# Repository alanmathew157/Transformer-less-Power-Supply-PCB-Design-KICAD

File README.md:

# TRANSFORMER LESS POWER SUPPLY PCB Design using KICAD -ALTIMUM
## PCB TOP VIEW

## PCB BOTTOM VIEW

## Project Overview
This project is a transformerless power supply designed in KiCad as part of my PCB design learning journey. Instead of using a bulky step-down transformer, the circuit employs a capacitive dropper (C4) to limit the AC current from the mains supply. The series resistor helps limit inrush current and improve safety. The reduced AC signal is then rectified using a full-wave bridge rectifier composed of four 1N4007 diodes, converting it into pulsating DC. Filter capacitors (C1, C2, and C3) smooth the rectified voltage by reducing ripple. Zener diodes provide voltage clamping and protection against overvoltage conditions. Finally, an LM7805 linear voltage regulator produces a stable 5V DC output suitable for low-power electronic applications. An LED indicator with a current-limiting resistor confirms the presence of output voltage.

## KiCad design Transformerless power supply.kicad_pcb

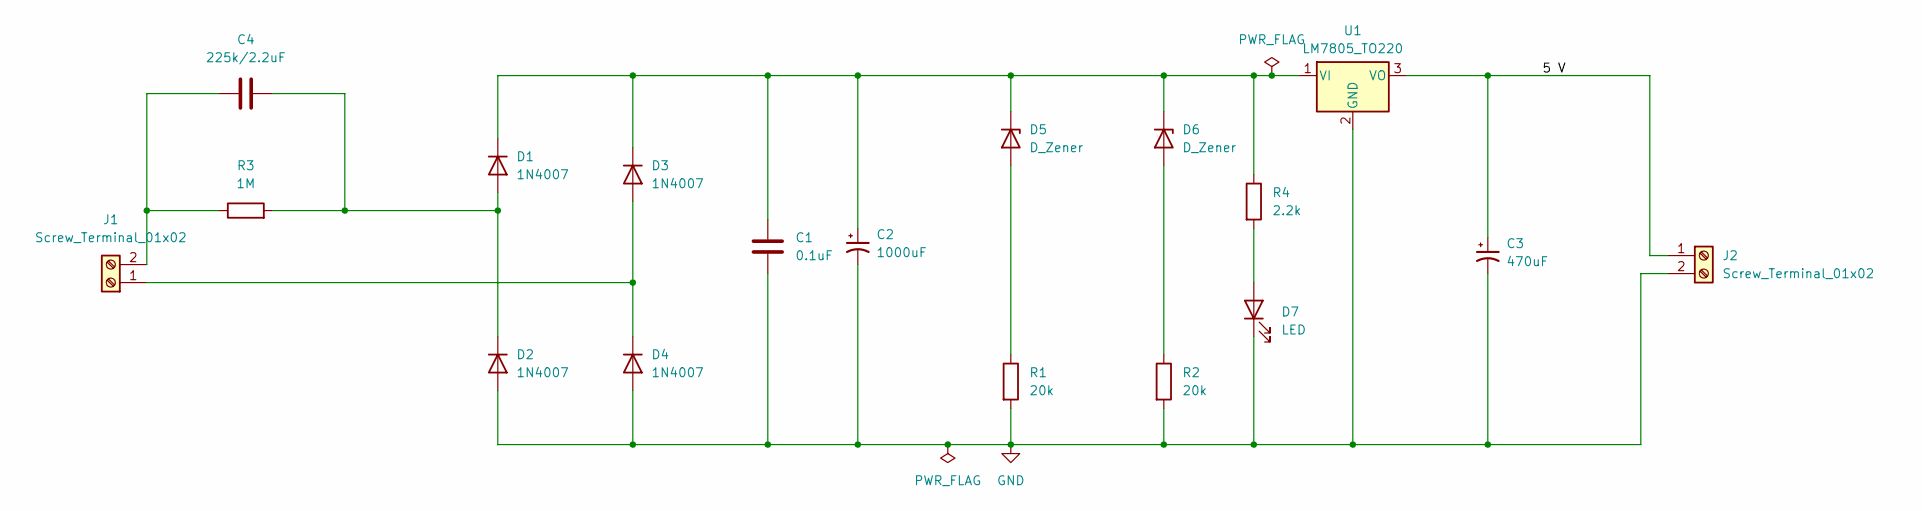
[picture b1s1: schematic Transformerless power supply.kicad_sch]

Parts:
C1: 0.1uF; C_Disc_D4.7mm_W2.5mm_P5.00mm
C2: 1000uF; CP_Radial_D10.0mm_P5.00mm
C3: 470uF; CP_Radial_D10.0mm_P3.80mm
C4: 225k/2.2uF; C_Rect_L18.0mm_W6.0mm_P15.00mm_FKS3_FKP3
D1, D2, D3, D4: 1N4007; D_DO-41_SOD81_P10.16mm_Horizontal
D5, D6: D_Zener; D_A-405_P7.62mm_Horizontal
D7: LED; LED_D5.0mm
J1, J2: Screw_Terminal_01x02; TerminalBlock_CUI_TB007-508-02_1x02_P5.08mm_Horizontal
R1, R2: 20k; R_Axial_DIN0207_L6.3mm_D2.5mm_P7.62mm_Horizontal
R3: 1M; R_Axial_DIN0207_L6.3mm_D2.5mm_P7.62mm_Horizontal
R4: 2.2k; R_Axial_DIN0207_L6.3mm_D2.5mm_P7.62mm_Horizontal
U1: LM7805_TO220; TO-220-3_Vertical

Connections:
/5 V: C3.1, J2.1, U1.3 (VO)
GND: C1.2, C2.2, C3.2, D2.2 (A), D4.2 (A), D7.1 (K), J2.2, R1.2, R2.2, U1.2 (GND)
unnamed: C4.1, D1.2 (A), D2.1 (K), R3.2
unnamed: C1.1, C2.1, D1.1 (K), D3.1 (K), D5.1 (K), D6.1 (K), R4.1, U1.1 (VI)
unnamed: D3.2 (A), D4.1 (K), J1.1
unnamed: D5.2 (A), R1.1
unnamed: D6.2 (A), R2.1
unnamed: D7.2 (A), R4.2
unnamed: C4.2, J1.2, R3.1

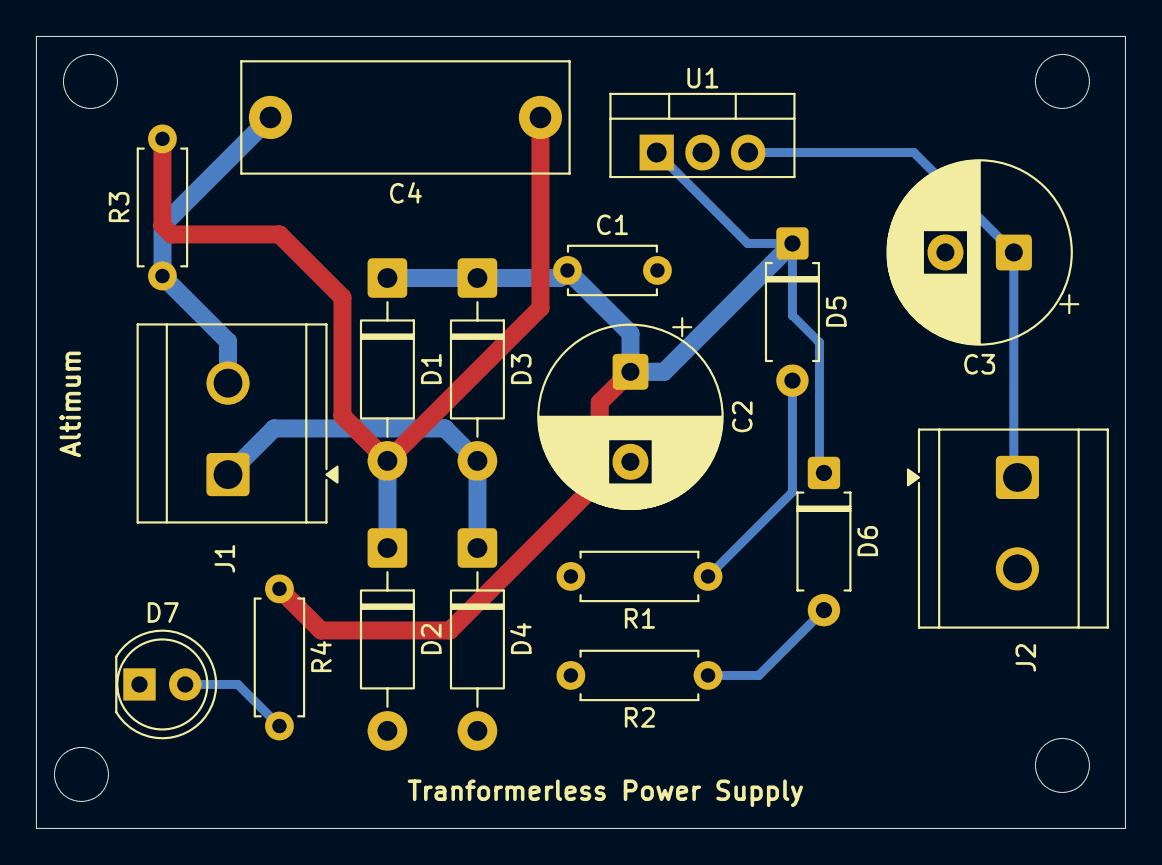
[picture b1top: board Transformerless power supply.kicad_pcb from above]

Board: 2 copper layers, 60.5 x 44.0 mm, 18 parts (0 on the bottom side), 9 nets.

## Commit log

2026-03-01 Add README with project details and PCB images
    Added project overview and images of PCB views.
2026-03-01 Expand project overview with learning context
    Added a personal learning note about KiCad and transformer-less power supply circuits.
2026-03-01 Enhance project overview with detailed component descriptions
    Expanded the project overview to include specific component details and their functions in the transformer-less power supply circuit.
2026-03-01 Revise project overview for clarity and detail
    Updated project overview to clarify circuit design and components.
